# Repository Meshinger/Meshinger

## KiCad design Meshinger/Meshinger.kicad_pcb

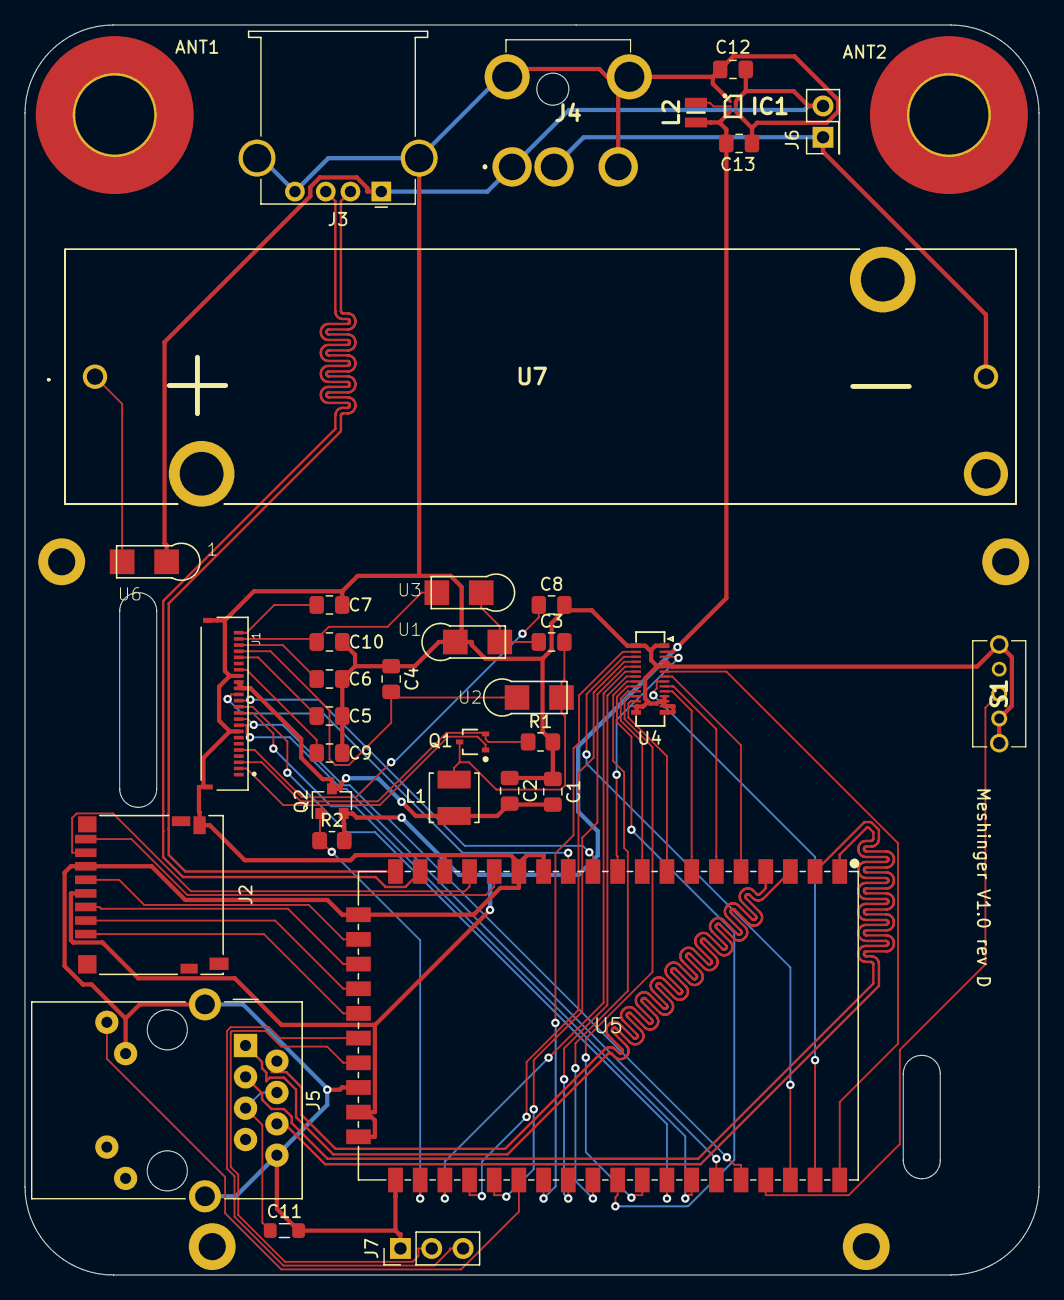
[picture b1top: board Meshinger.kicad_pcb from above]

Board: 2 copper layers, 82.2 x 101.3 mm, 41 parts (0 on the bottom side), 59 nets.

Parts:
ANT1, ANT2: MountingHole_6.4mm_M6_Pad_TopBottom
C1: 0.1uF/16V; C_0805_2012Metric_Pad1.18x1.45mm_HandSolder
C2: 1uF/6.3V; C_0805_2012Metric_Pad1.18x1.45mm_HandSolder
C3: 4.7uF/25V; C_0805_2012Metric_Pad1.18x1.45mm_HandSolder
C4, C5, C6, C7, C8, C9, C10: 1uF/25V; C_0805_2012Metric_Pad1.18x1.45mm_HandSolder
C11: 0.1uF; L_0805_2012Metric_Pad1.05x1.20mm_HandSolder
C12: 2.2uF; C_0805_2012Metric_Pad1.18x1.45mm_HandSolder
C13: 10uF; C_0805_2012Metric_Pad1.18x1.45mm_HandSolder
IC1: FAN53610AUC33X; BGA6C40P2X3_86X116X62
J1: FH34SRJ-24S-0.5SH(99); HRS_FH34SRJ-24S-0.5SH(99)
J2: Micro_SD_Card; microSD_HC_Hirose_DM3D-SF
J3: USB_A; USB_A_Stewart_SS-52100-001_Horizontal
J4: Barrel_Jack_Switch; PJ079BH
J5: RJ45_Amphenol_RJMG1BD3B8K1ANR
J6: Conn_02x01; PinHeader_2x01_P2.54mm_Vertical
J7: Conn_01x03; PinHeader_1x03_P2.54mm_Vertical
L1: 10uH; IND_LQH44PN100MJ0L
L2: LQM2MPN1R0MGHL; LQM2MPN1R0NG0L
MH_CASE1, MH_CASE2: MountingHole_2.2mm_M2_DIN965_Pad
MH_KBD1, MH_KBD2: MountingHole_2.2mm_M2_DIN965_Pad
Q1: MCH3478-TL-W; On_Semiconductor-MCH3478-TL-H-Manufacturer_Recommended
Q2: NTR2101P; SOT-23
R1: 0.47ohm; R_0805_2012Metric_Pad1.20x1.40mm_HandSolder
R2: 10k; R_0805_2012Metric_Pad1.20x1.40mm_HandSolder
S1: 1825232-1; 18252321
U1, U2, U3, U6: SS2040FL; SOD-123FL
U4: BBQ10KBD; BM14B(0.8)-24DS-0.4V(53)
U5: SKW92A; SKYLAB_SKW92A
U7: 1043

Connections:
+3V3: C13.1, IC1.C1, J2.4, L2.2, Q2.2, R2.2, U4.2, U5.28, U5.29
BAT+: C12.1, IC1.A2, IC1.B2, J3.1, J4.1, J6.2, U6.1
BAT-: J4.3, J6.1, U7.2
COL1: U4.7, U5.5
COL2: U4.9, U5.6
COL3: U4.10, U5.7
COL4: U4.17, U5.8
COL5: U4.19, U5.9
Display_Power_Switch: C1.2, C2.2, J1.15, J1.16, L1.2, Q2.3
EINK_CHIP_SELECT: J1.12, U5.41
EINK_DATA_COMMAND: J1.11, U5.42
EINK_DISPLAY_BUSY: J1.9, U5.43
EINK_DISPLAY_RESET: J1.10, U5.44
GND: C1.1, C2.1, C4.1, C5.2, C6.1, C7.2, C8.2, C9.2, C10.2, C11.2, C12.2, C13.2, IC1.A1, IC1.C2, J1.8, J1.17, J1.S1, J1.S2, J2.6, J2.9, J3.4, J3.5, J4.2, J4.MH1, J4.MH2, J5.13, J5.L3, J5.R8, J7.1, R1.2, S1.1, S1.MH1, S1.MH2, U1.1, U4.1, U4.4, U4.5, U4.11, U4.12, U4.13, U4.14, U4.15, U4.16, U4.28, U5.13, U5.14, U5.17, U5.20, U5.27, U5.30
GPIO: U4.26, U5.46
HW_RESET: S1.2, U5.45
LAN1_RX+: J5.R3, U5.1
LAN1_RX-: J5.R6, U5.2
LAN1_TX+: J5.R1, U5.3
LAN1_TX-: J5.R2, U5.4
LED0: J5.L4, U5.35
LED1: U4.24, U5.34
LED2: U4.25, U5.33
LED3: U4.23, U5.32
unnamed: C3.1, U1.2, U3.1
unnamed: C3.2, L1.1, Q1.3, U2.2
unnamed: C4.2, J1.21, U2.1
unnamed: C5.1, J1.20
unnamed: C6.2, J1.23, U3.2
unnamed: C7.1, J1.24
unnamed: C8.1, J1.5
unnamed: C9.1, J1.18
unnamed: C10.1, J1.22
unnamed: C11.1, J5.R4, J5.R5
unnamed: IC1.B1, L2.1
unnamed: J1.2, Q1.1
unnamed: J1.3, Q1.2, R1.1
unnamed: J2.1, U5.24
unnamed: J2.2, U5.23
unnamed: J2.3, U5.22
unnamed: J2.5, U5.21
unnamed: J2.7, U5.16
unnamed: J2.8, U5.15
unnamed: Q2.1, R2.1, U5.31
unnamed: U6.2, U7.1
PWM: U4.3, U5.10
ROW1: U4.6, U5.48
ROW2: U4.8, U5.47
ROW3: U4.18, U5.40
ROW4: U4.20, U5.39
ROW5: U4.21, U5.38
ROW6: U4.22, U5.37
ROW7: U4.27, U5.36
SPI_CLK: J1.13, U5.11
SPI_MOSI: J1.14, U5.12
UART_RX: J7.3, U5.25
UART_TX: J7.2, U5.26
USB+: J3.3, U5.18
USB-: J3.2, U5.19

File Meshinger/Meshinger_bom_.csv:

Component,Description,Part,References,Value,Footprint,Quantity Per PCB,Datasheet,MAXIMUM_PACKAGE_HEIGHT,STANDARD,PARTREV,MANUFACTURER,Component Link 1 URL,Component Link 1 Description,VBRDSS Min V,VGSth Max V,category,imported,Coss Typ pF,Channel Polarity,ciiva ids,Packing,Package Type,Configuration,release date,rohs,vault revision,VGS Max V,Component Link 3 Description,Package Description,manufacturer,library id,package,Ciss Typ pF,Crss Typ pF,Mounting Technology,Component Link 3 URL
1,Unpolarized capacitor,C,C1,0.1uF/16V,C_0805_2012Metric_Pad1.18x1.45mm_HandSolder,1,~,,,,,,,,,,,,,,,,,,,,,,,,,,,,,
2,Unpolarized capacitor,C,C4 C5 C6 C7 C8 C9 C10,1uF/25V,C_0805_2012Metric_Pad1.18x1.45mm_HandSolder,7,~,,,,,,,,,,,,,,,,,,,,,,,,,,,,,
3,Unpolarized capacitor,C,C2,1uF/6.3V,C_0805_2012Metric_Pad1.18x1.45mm_HandSolder,1,~,,,,,,,,,,,,,,,,,,,,,,,,,,,,,
4,Unpolarized capacitor,C,C3,4.7uF/25V,C_0805_2012Metric_Pad1.18x1.45mm_HandSolder,1,~,,,,,,,,,,,,,,,,,,,,,,,,,,,,,
5,"Generic connector, double row, 02x01, this symbol is compatible with counter-clockwise, top-bottom and odd-even numbering schemes., script generated (kicad-library-utils/schlib/autogen/connector/)",Conn_02x01,J4,Conn_02x01,PinHeader_2x01_P2.54mm_Vertical,1,~,,,,,,,,,,,,,,,,,,,,,,,,,,,,,
6,"Generic connector, double row, 02x06, odd/even pin numbering scheme (row 1 odd numbers, row 2 even numbers), script generated (kicad-library-utils/schlib/autogen/connector/)",Conn_02x06_Odd_Even,J1,Conn_02x06_Odd_Even,PinHeader_2x06_P2.54mm_Vertical,1,~,,,,,,,,,,,,,,,,,,,,,,,,,,,,,
7,,FH34SRJ-24S-0.5SH(99),J3,FH34SRJ-24S-0.5SH(99),HRS_FH34SRJ-24S-0.5SH(99),1,,1.75mm,Manufacturer Recommendations,NA,HIROSE ELECTRIC,,,,,,,,,,,,,,,,,,,,,,,,,
8,Micro SD Card Socket,Micro_SD_Card,J2,Micro_SD_Card,microSD_HC_Hirose_DM3D-SF,1,http://katalog.we-online.de/em/datasheet/693072010801.pdf,,,,,,,,,,,,,,,,,,,,,,,,,,,,,
9,Inductor,L,L1,10uH,L_0805_2012Metric_Pad1.15x1.40mm_HandSolder,1,~,,,,,,,,,,,,,,,,,,,,,,,,,,,,,
10,MCH3478-TL-H,MCH3478-TL-H,Q1,MCH3478-TL-W,On_Semiconductor-MCH3478-TL-H-Manufacturer_Recommended,1,http://www.onsemi.cn/pub_link/Collateral/ENAA1353-D.PDF,,,,,http://www.onsemi.com/,Manufacturer URL,30,1.3,Trans,yes,21,N Channel,837008,Tape and Reel,SC-70FL / MCPH-3,Single,1407149804,No,4F433114-B412-42D1-93FA-4D10C81BF666,12,Package Specification,"3-Pin Small Outline Transistor, Body 2 x 1.6 mm, Pitch 0.65 mm",On Semiconductor,1afd2ccbcc2ba532,MCPH-3,130,14,Surface Mount,http://www.onsemi.com/pub_link/Collateral/EN7354-D.PDF
11,"-3.7A Id, -8V Vds, P-Channel MOSFET, SOT-23",NTR2101P,Q2,NTR2101P,SOT-23,1,http://www.onsemi.com/pub/Collateral/NTR2101P-D.PDF,,,,,,,,,,,,,,,,,,,,,,,,,,,,,
12,Resistor,R,R1,0.47ohm,R_0805_2012Metric_Pad1.20x1.40mm_HandSolder,1,~,,,,,,,,,,,,,,,,,,,,,,,,,,,,,
13,,BBQ10KBD,U2,BBQ10KBD,BM14B(0.8)-24DS-0.4V(53),1,,,,,,,,,,,,,,,,,,,,,,,,,,,,,,
14,Skylab 802.11b/g/n Module,SKW92A,U1,SKW92A,SKYLAB_SKW92A,1,http://www.skylab.com.cn/uploadfile/Download/SkyLab_SKW92A_V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,,,,,,,,,,,,,,,,,,,,,,,,,,,,,
15,,SS2040FL,U3 U4 U5,SS2040FL,SOD-123FL,3,,,,,,,,,,,,,,,,,,,,,,,,,,,,,,





Component Groups:,15
Component Count:,23
Fitted Components:,23
Number of PCBs:,1
Total components:,23
Schematic Version:,
Schematic Date:,
PCB Variant:,default
BoM Date:,"Sunday, February 28, 2021 at 01:30:17 PM"
Schematic Source:,Meshinger.sch
KiCad Version:,Eeschema (5.1.9-0-10_14)

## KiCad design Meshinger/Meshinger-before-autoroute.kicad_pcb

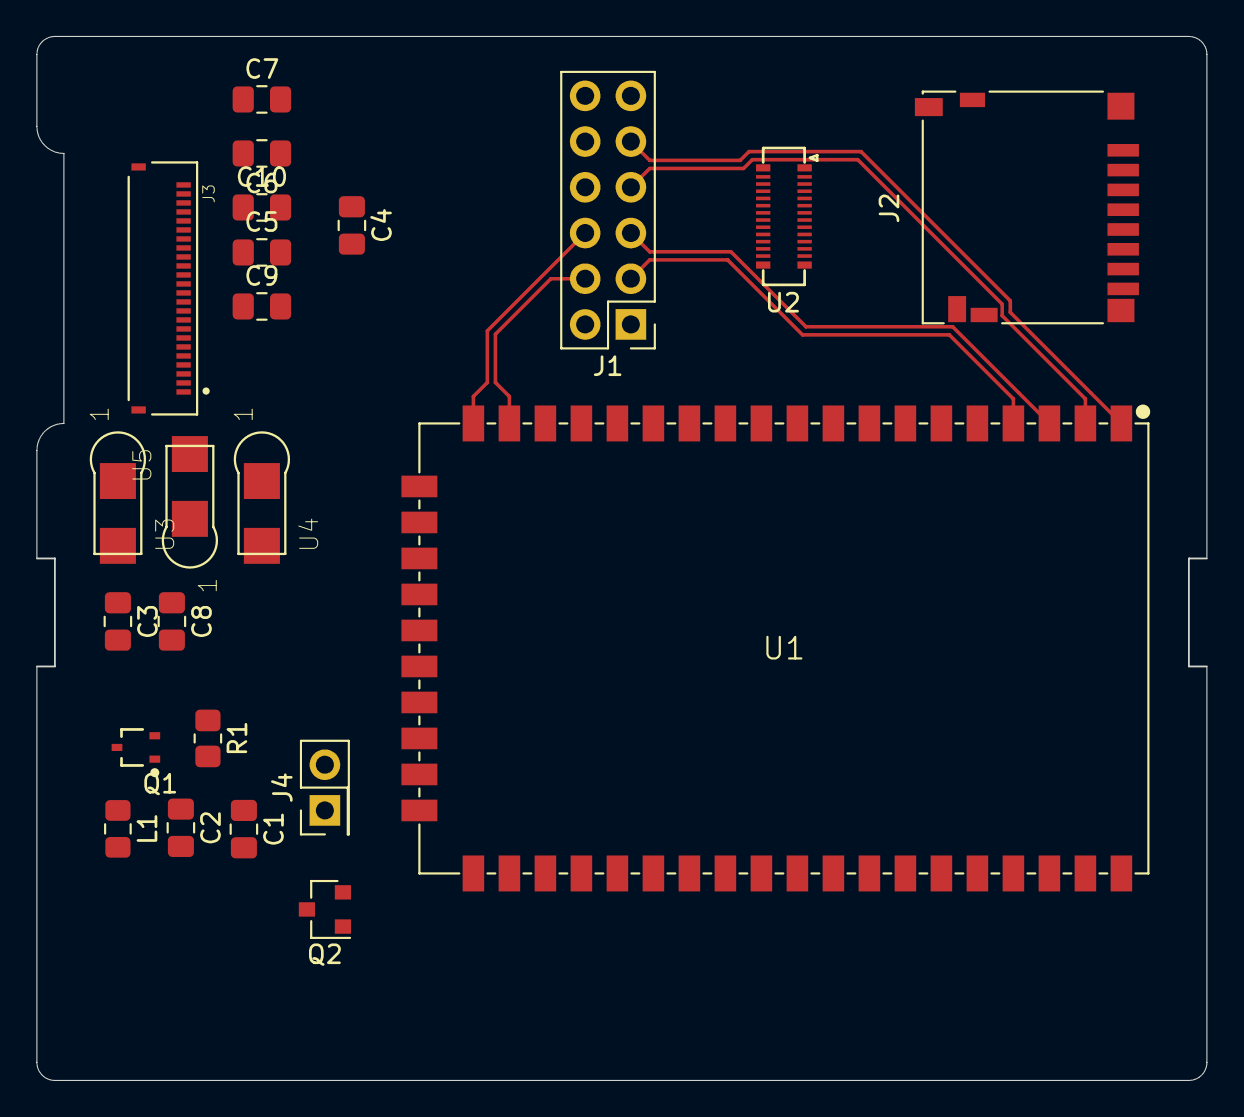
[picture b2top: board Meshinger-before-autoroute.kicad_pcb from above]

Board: 2 copper layers, 65.0 x 58.0 mm, 23 parts (0 on the bottom side), 54 nets.

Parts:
C1: 0.1uF/16V; C_0805_2012Metric_Pad1.18x1.45mm_HandSolder
C2: 1uF/6.3V; C_0805_2012Metric_Pad1.18x1.45mm_HandSolder
C3: 4.7uF/25V; C_0805_2012Metric_Pad1.18x1.45mm_HandSolder
C4, C5, C6, C7, C8, C9, C10: 1uF/25V; C_0805_2012Metric_Pad1.18x1.45mm_HandSolder
J1: Conn_02x06_Odd_Even; PinHeader_2x06_P2.54mm_Vertical
J2: Micro_SD_Card; microSD_HC_Hirose_DM3D-SF
J3: FH34SRJ-24S-0.5SH(99); HRS_FH34SRJ-24S-0.5SH(99)
J4: Conn_02x01; PinHeader_2x01_P2.54mm_Vertical
L1: 10uH; L_0805_2012Metric_Pad1.15x1.40mm_HandSolder
Q1: MCH3478-TL-W; On_Semiconductor-MCH3478-TL-H-Manufacturer_Recommended
Q2: NTR2101P; SOT-23
R1: 0.47ohm; R_0805_2012Metric_Pad1.20x1.40mm_HandSolder
U1: SKW92A; SKYLAB_SKW92A
U2: BBQ10KBD; BM14B(0.8)-24DS-0.4V(53)
U3, U4, U5: SS2040FL; SOD-123FL

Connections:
+3V3: J1.2, J2.4, J4.1, Q2.2, U1.28, U1.29, U2.2
COL1: U1.5, U2.7
COL2: U1.6, U2.9
COL3: U1.7, U2.10
COL4: U1.8, U2.17
COL5: U1.9, U2.19
Display_Power_Switch: C1.2, C2.2, J3.15, J3.16, L1.2, Q2.3
EINK_CHIP_SELECT: J3.12, U1.41
EINK_DATA_COMMAND: J3.11, U1.42
EINK_DISPLAY_BUSY: J3.9, U1.43
EINK_DISPLAY_RESET: J3.10, U1.44
GND: C1.1, C2.1, C4.1, C5.2, C6.1, C7.2, C8.2, C9.2, C10.2, J1.1, J2.6, J2.9, J3.8, J3.17, J3.S1, J3.S2, J4.2, R1.2, U1.13, U1.14, U1.17, U1.20, U1.27, U1.30, U2.1, U2.4, U2.5, U2.11, U2.12, U2.13, U2.14, U2.15, U2.16, U2.28, U3.1
GPIO: J1.10, U1.46
HW_RESET: J1.8, U1.45
LAN1_RX+: J1.9, U1.1
LAN1_RX-: J1.7, U1.2
LAN1_TX+: J1.5, U1.3
LAN1_TX-: J1.3, U1.4
LED0: U1.35, U2.26
LED1: U1.34, U2.24
LED2: U1.33, U2.25
LED3: U1.32, U2.23
unnamed: C3.1, U3.2, U5.1
unnamed: C3.2, L1.1, Q1.3, U4.2
unnamed: C4.2, J3.21, U4.1
unnamed: C5.1, J3.20
unnamed: C6.2, J3.23, U5.2
unnamed: C7.1, J3.24
unnamed: C8.1, J3.5
unnamed: C9.1, J3.18
unnamed: C10.1, J3.22
unnamed: J2.1, U1.24
unnamed: J2.2, U1.23
unnamed: J2.3, U1.22
unnamed: J2.5, U1.21
unnamed: J2.7, U1.16
unnamed: J2.8, U1.15
unnamed: J3.2, Q1.1
unnamed: J3.3, Q1.2, R1.1
unnamed: Q2.1, U1.31
PWM: U1.10, U2.3
ROW1: U1.48, U2.6
ROW2: U1.47, U2.8
ROW3: U1.40, U2.18
ROW4: U1.39, U2.20
ROW5: U1.38, U2.21
ROW6: U1.37, U2.22
ROW7: U1.36, U2.27
SPI_CLK: J3.13, U1.11
SPI_MOSI: J3.14, U1.12
UART_RX: J1.11, U1.25
UART_TX: J1.12, U1.26
USB+: J1.4, U1.18
USB-: J1.6, U1.19

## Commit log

2021-03-01 Initial Commit, V1.0 rev A
2021-06-23 Meshinger 1.0 rev B WARNING THE DC PLUG PINS ARE WRONG, SHORTS BATTERY!
2021-10-07 Meshinger 1.0 rev C, Display Power MOSFET heats up while off...
2021-10-29 Added mosfet datasheet
2022-02-26 Meshinger 1.0 rev D, now with power switch and squiggles.
